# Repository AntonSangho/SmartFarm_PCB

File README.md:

# 프로젝트명 : 포르쉐 

# 요구사항 작성을 위한 질문 
- 수집하고자하는 환경데이터: 예) 온도, 습도  
- 휴대가능여부 
- 물리적인 사이즈 : 예) 휴대폰사이즈 , 카드지갑사이즈 
- 사용자가 손으로 제어하는 방식 : 예) 버튼
- 사용자가 동작을 확인하는 형태 : 예) LED, 부저음, 액정디스플레이
- 데이터를 확인하는 시각적인 결과물의 형태 : 예) 로우데이터, 그래프 
- 생각하는 키트의 외관 형태 
- 베터리로 동작하는 경우, 사용가능해야하는 대략적인 시간 
- 제작 수량

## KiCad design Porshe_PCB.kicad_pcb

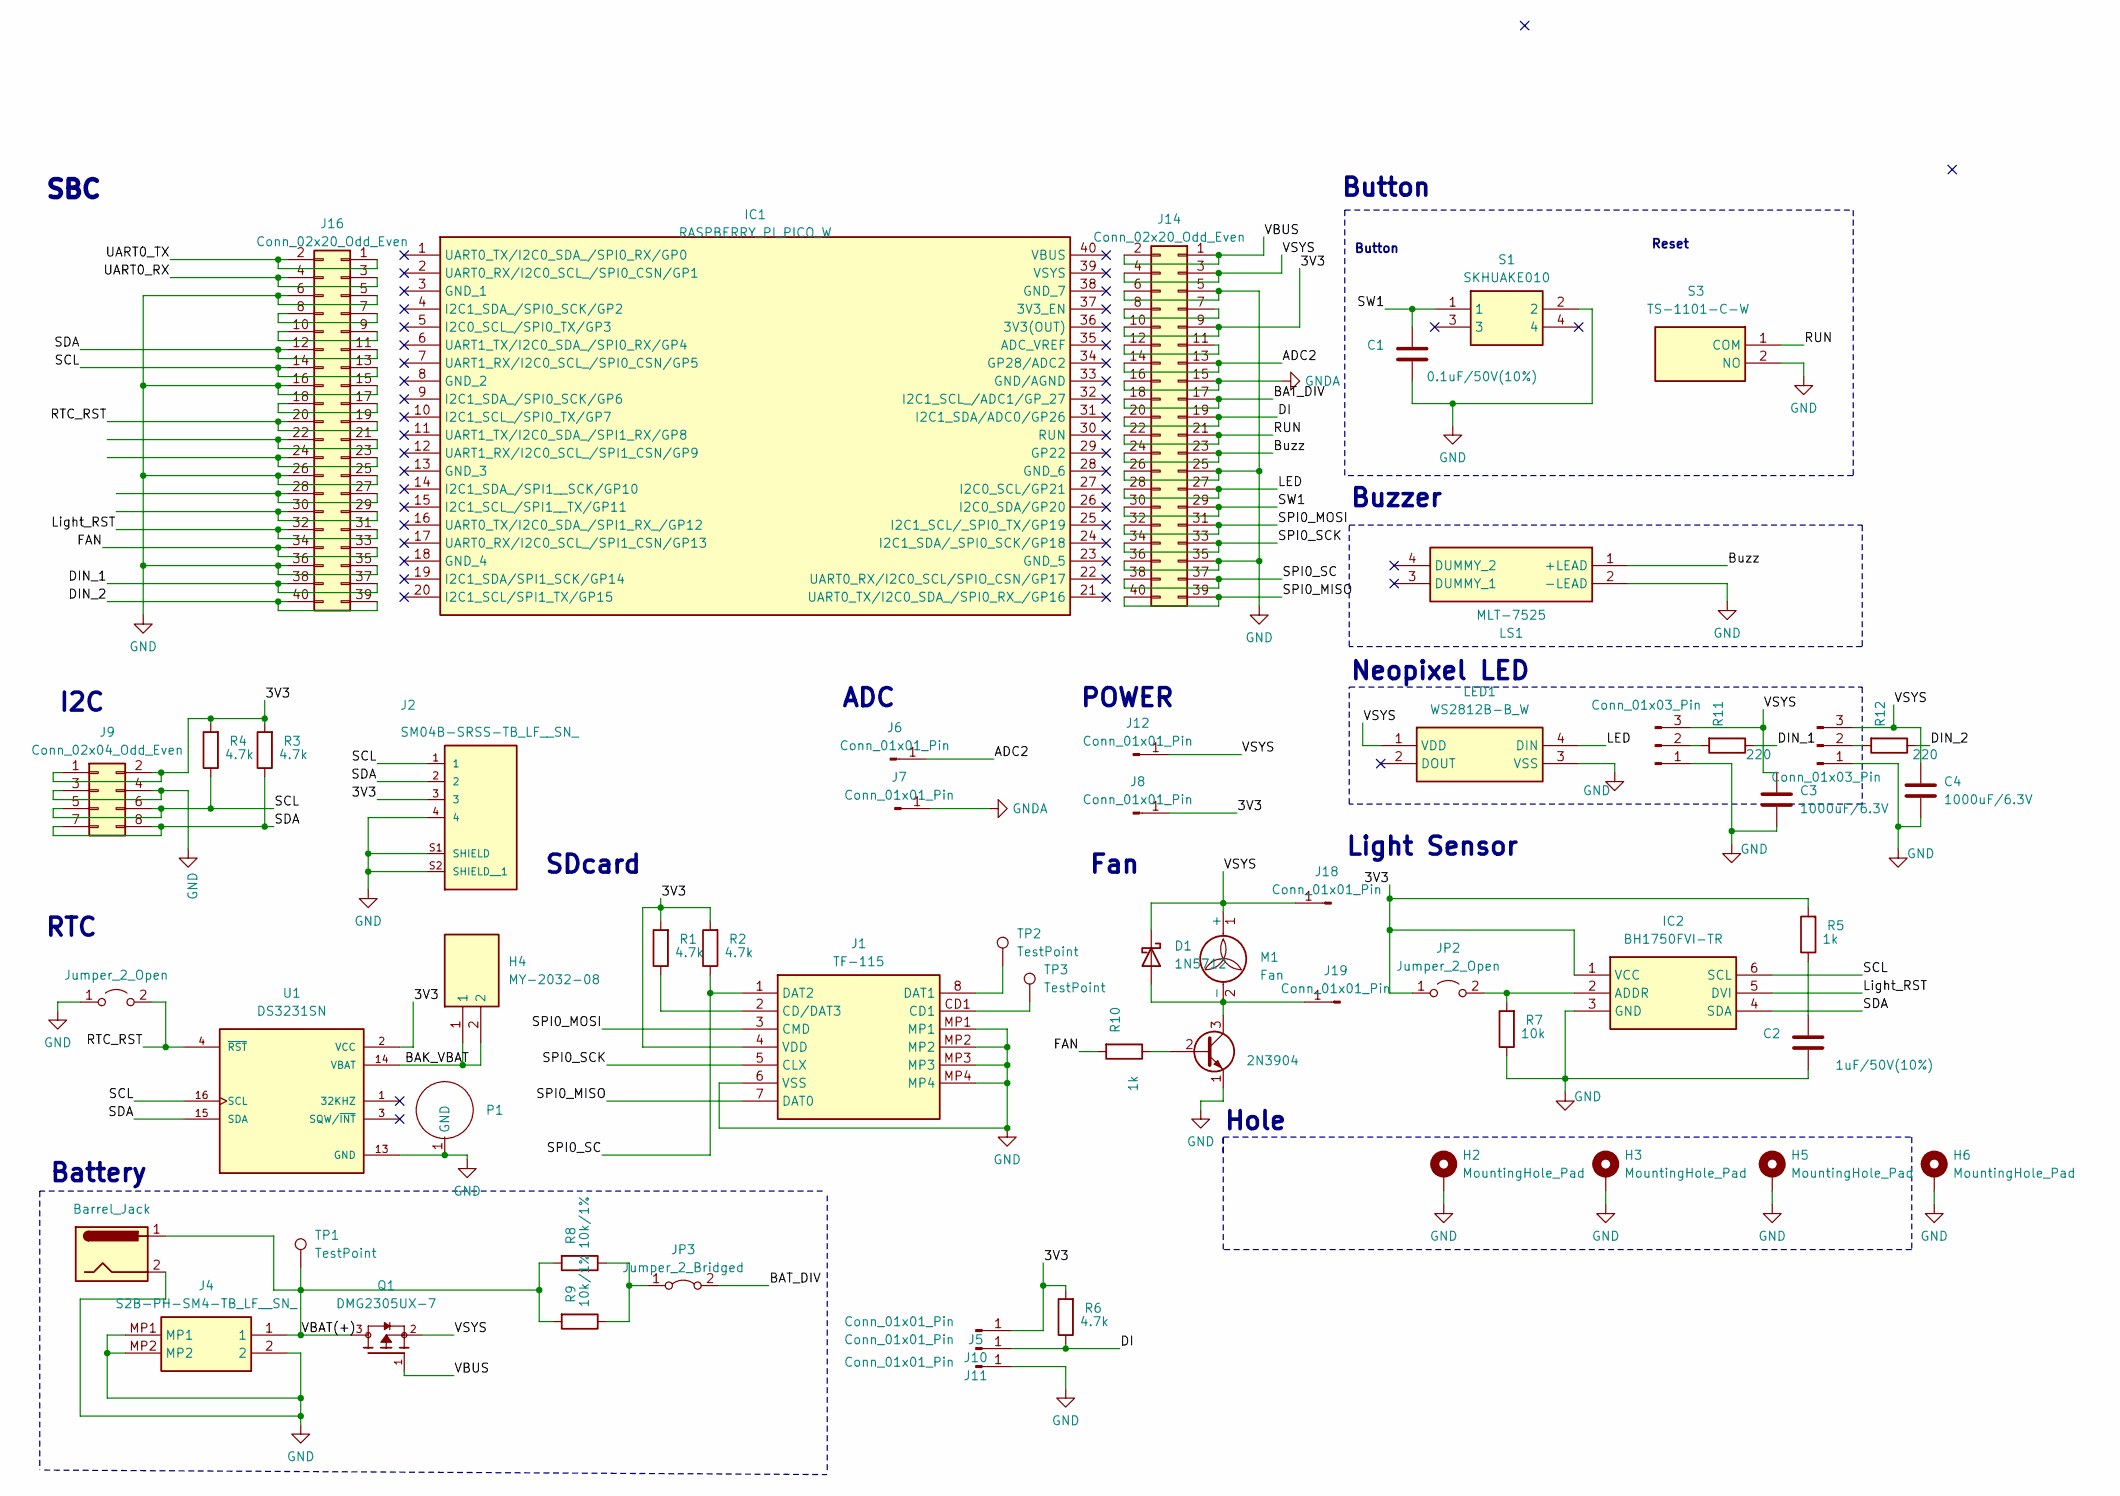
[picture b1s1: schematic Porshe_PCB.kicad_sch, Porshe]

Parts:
C1: 0.1uF/50V(10%); C_0603_1608Metric; LCSC Part # C14663
C2: 1uF/50V(10%); C_0603_1608Metric; LCSC Part # C14663
C3, C4: 1000uF/6.3V; CP_Radial_D8.0mm_P5.00mm
D1: 1N5712; D_DO-35_SOD27_P7.62mm_Horizontal
H2, H3, H5, H6: MountingHole_Pad; MountingHole_2.7mm_M2.5_ISO7380_Pad_TopOnly
H4: MY-2032-08; MY203208; Manufacturer_Part_Number MY-2032-08; JLCPCB Part # C964831
IC1: RASPBERRY_PI_PICO_W; RASPBERRYPIPICOW; Manufacturer_Part_Number RASPBERRY PI PICO W
IC2: BH1750FVI-TR; WSOF6; Manufacturer_Part_Number BH1750FVI-TR; Mouser Part Number 755-BH1750FVI-TR
J1: TF-115; TF115; Manufacturer_Part_Number TF-115; LCSC Part # C266620
J2: SM04B-SRSS-TB_LF__SN_; JST_SM04B-SRSS-TB_LF__SN_; LCSC Part # C160404
J4: S2B-PH-SM4-TB_LF__SN_; S2BPHSM4TBLFSN; Manufacturer_Part_Number S2B-PH-SM4-TB(LF)(SN); LCSC Part # C295747
J5, J10, J11, J12: Conn_01x01_Pin; TestPoint_THTPad_D2.0mm_Drill1.0mm
J6, J7, J8, J18, J19: Conn_01x01_Pin; Pin_D1.3mm_L11.0mm
J9: Conn_02x04_Odd_Even; PinSocket_2x04_P2.54mm_Vertical_SMD; LCSC Part # C5160819
J13: Barrel_Jack; BarrelJack_GCT_DCJ200-10-A_Horizontal
J14, J16: Conn_02x20_Odd_Even; PinSocket_2x20_P2.54mm_Vertical_SMD; LCSC Part # C3975165
J15, J17: Conn_01x03_Pin; PinHeader_1x03_P2.00mm_Vertical
JP1, JP2: Jumper_2_Open; SolderJumper-2_P1.3mm_Open_RoundedPad1.0x1.5mm
JP3: Jumper_2_Bridged; SolderJumper-2_P1.3mm_Bridged_RoundedPad1.0x1.5mm
LED1: WS2812B-B_W; WS2812BBW; Manufacturer_Part_Number WS2812B-B/W; JLCPCB Part # C2761795
LS1: MLT-7525; MLT7525; Manufacturer_Part_Number MLT-7525
M1: Fan
P1: CR2032_GND
Q1: DMG2305UX-7; SOT91P240X110-3N_DMG2305UX-7; PARTREV 09/2018; LCSC Part # C150470
Q2: 2N3904; TO-92_Inline
R1, R2, R3, R4, R6: 4.7k; R_0603_1608Metric_Pad0.98x0.95mm_HandSolder
R5, R10: 1k; R_0603_1608Metric_Pad0.98x0.95mm_HandSolder
R7: 10k; R_0603_1608Metric_Pad0.98x0.95mm_HandSolder
R8, R9: 10k/1%; R_0603_1608Metric_Pad0.98x0.95mm_HandSolder
R11, R12: 220; R_0603_1608Metric_Pad0.98x0.95mm_HandSolder
S1: SKHUAKE010; Manufacturer_Part_Number SKHUAKE010; Mouser Part Number 688-SKHUAKE010
S3: TS-1101-C-W; TS1101CW; Manufacturer_Part_Number TS-1101-C-W
TP1, TP2, TP3: TestPoint; TestPoint_Pad_D1.0mm
U1: DS3231SN; SOIC127P1032X265-16N

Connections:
/3V3: IC2.1 (VCC), J1.4 (VDD), J2.3, J5.1, J8.1, J9.1, J9.2, J14.9, J14.10, JP2.1 (A), R1.2, R2.2, R3.2, R4.2, R5.2, R6.2, U1.2 (VCC)
/ADC2: J6.1, J14.13, J14.14
/BAK_VBAT: H4.1, H4.2, U1.14 (VBAT)
/BAT_DIV: J14.17, J14.18, JP3.2 (B)
/Buzz: J14.23, J14.24, LS1.1 (+LEAD)
/DI: J10.1, J14.19, J14.20, R6.1
/DIN_1: J16.37, J16.38, R11.1
/DIN_2: J16.39, J16.40, R12.1
/FAN: J16.33, J16.34, R10.2
/LED: J14.27, J14.28, LED1.4 (DIN)
/Light_RST: IC2.5 (DVI), J16.31, J16.32
/RTC_RST: J16.19, J16.20, JP1.2 (B), U1.4 (~RST)
/RUN: J14.21, J14.22, S3.1 (COM)
/SCL: IC2.6 (SCL), J2.1, J9.5, J9.6, J16.13, J16.14, R4.1, U1.16 (SCL)
/SDA: IC2.4 (SDA), J2.2, J9.7, J9.8, J16.11, J16.12, R3.1, U1.15 (SDA)
/SPI0_MISO: J1.7 (DAT0), J14.39, J14.40
/SPI0_MOSI: J1.3 (CMD), J14.31, J14.32
/SPI0_SC: J1.1 (DAT2), J14.37, J14.38, R2.1
/SPI0_SCK: J1.5 (CLX), J14.33, J14.34
/SW1: C1.2, J14.29, J14.30, S1.1
/UART0_RX: J16.3, J16.4
/UART0_TX: J16.1, J16.2
/VBAT(+): J4.1, J13.1, Q1.3, R8.2, R9.2, TP1.1
/VBUS: J14.1, J14.2, Q1.1
/VSYS: C3.1, C4.1, D1.1 (K), J12.1, J14.3, J14.4, J15.3, J17.3, J18.1, LED1.1 (VDD), M1.1 (+), Q1.2
GND: C1.1, C2.1, C3.2, C4.2, H2.1, H3.1, H5.1, H6.1, IC2.3 (GND), J1.6 (VSS), J1.MP1, J1.MP2, J1.MP3, J1.MP4, J2.4, J2.S1 (SHIELD), J2.S2 (SHIELD__1), J4.2, J4.MP1, J4.MP2, J9.3, J9.4, J11.1, J13.2, J14.5, J14.6, J14.25, J14.26, J14.35, J14.36, J15.1, J16.5, J16.6, J16.15, J16.16, J16.25, J16.26, J16.35, J16.36, J17.1, JP1.1 (A), LED1.3 (VSS), LS1.2 (-LEAD), P1.1 (GND), Q2.1 (E), R7.1, S1.2, S3.2 (NO), U1.13 (GND)
GNDA: J7.1, J14.15, J14.16
unnamed: C2.2, R5.1
unnamed: D1.2 (A), J19.1, M1.2 (-), Q2.3 (C)
unnamed: IC2.2 (ADDR), JP2.2 (B), R7.2
unnamed: J1.2 (CD/DAT3), R1.1
unnamed: J1.8 (DAT1), TP2.1
unnamed: J1.CD1, TP3.1
unnamed: J14.7, J14.8
unnamed: J14.11, J14.12
unnamed: J15.2, R11.2
unnamed: J16.7, J16.8
unnamed: J16.9, J16.10
unnamed: J16.17, J16.18
unnamed: J16.21, J16.22
unnamed: J16.23, J16.24
unnamed: J16.27, J16.28
unnamed: J16.29, J16.30
unnamed: J17.2, R12.2
unnamed: JP3.1 (A), R8.1, R9.1
unnamed: Q2.2 (B), R10.1

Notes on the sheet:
Fan
Reset
I2C
POWER
Button
Button
Battery
RTC
Buzzer
Neopixel LED
SDcard
Hole
Light Sensor
ADC
SBC

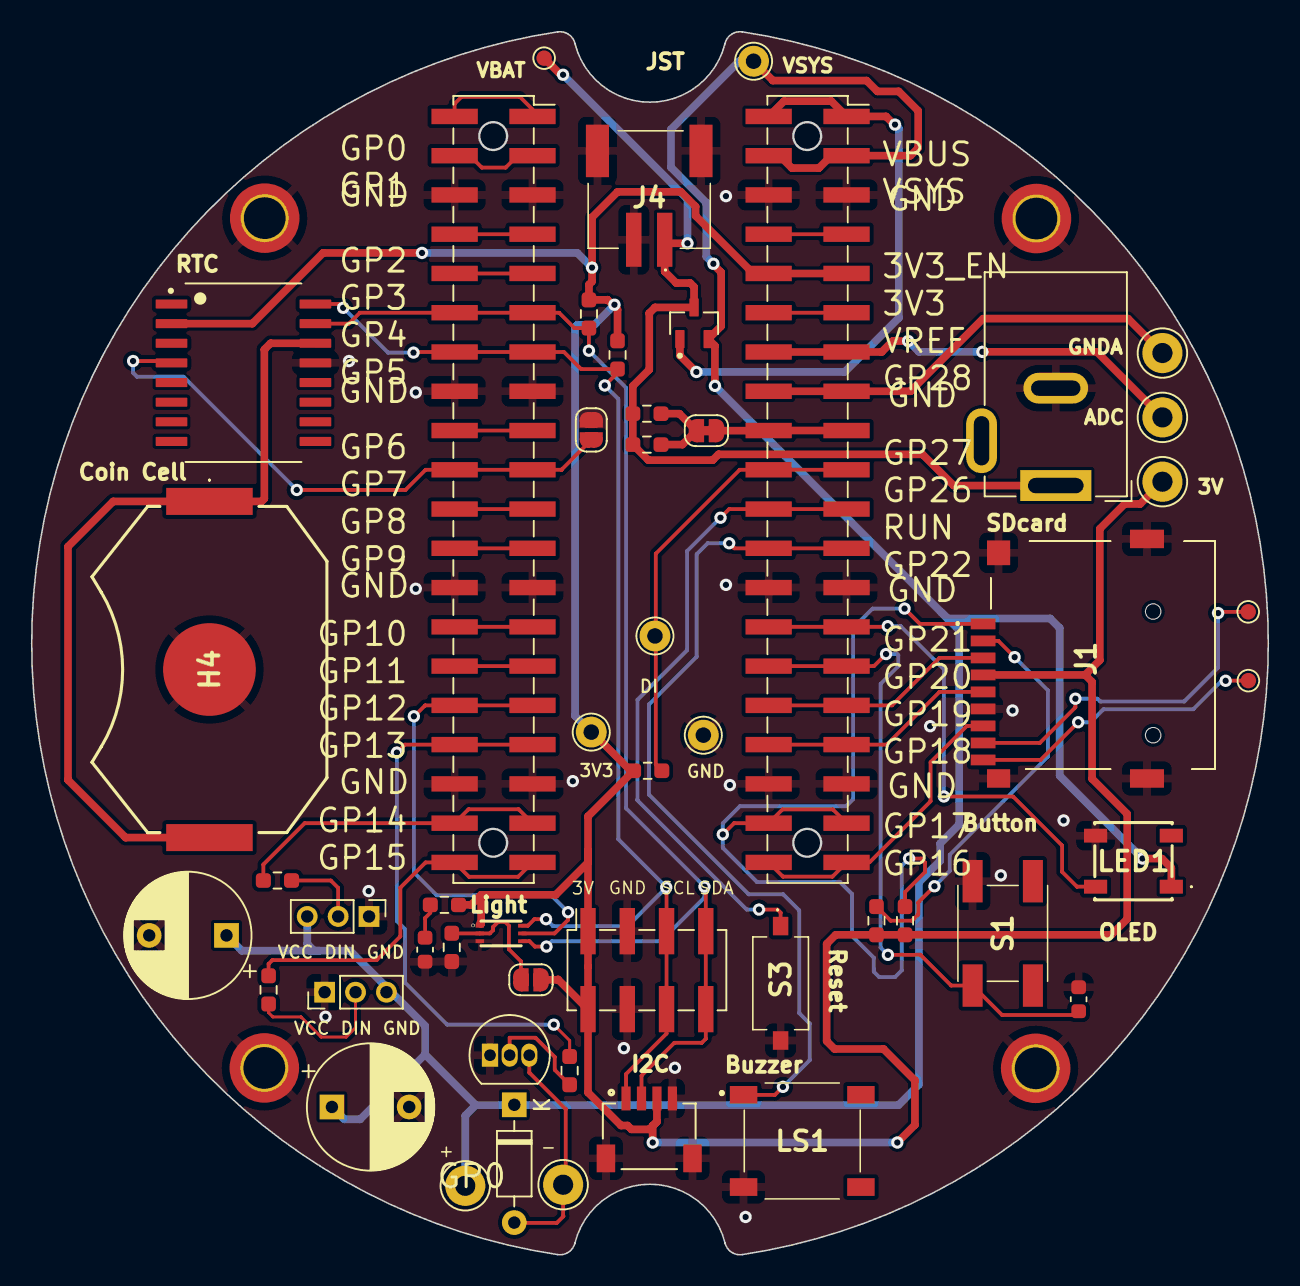
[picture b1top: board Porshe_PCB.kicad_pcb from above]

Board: 2 copper layers, 80.0 x 79.1 mm, 55 parts (0 on the bottom side), 46 nets.

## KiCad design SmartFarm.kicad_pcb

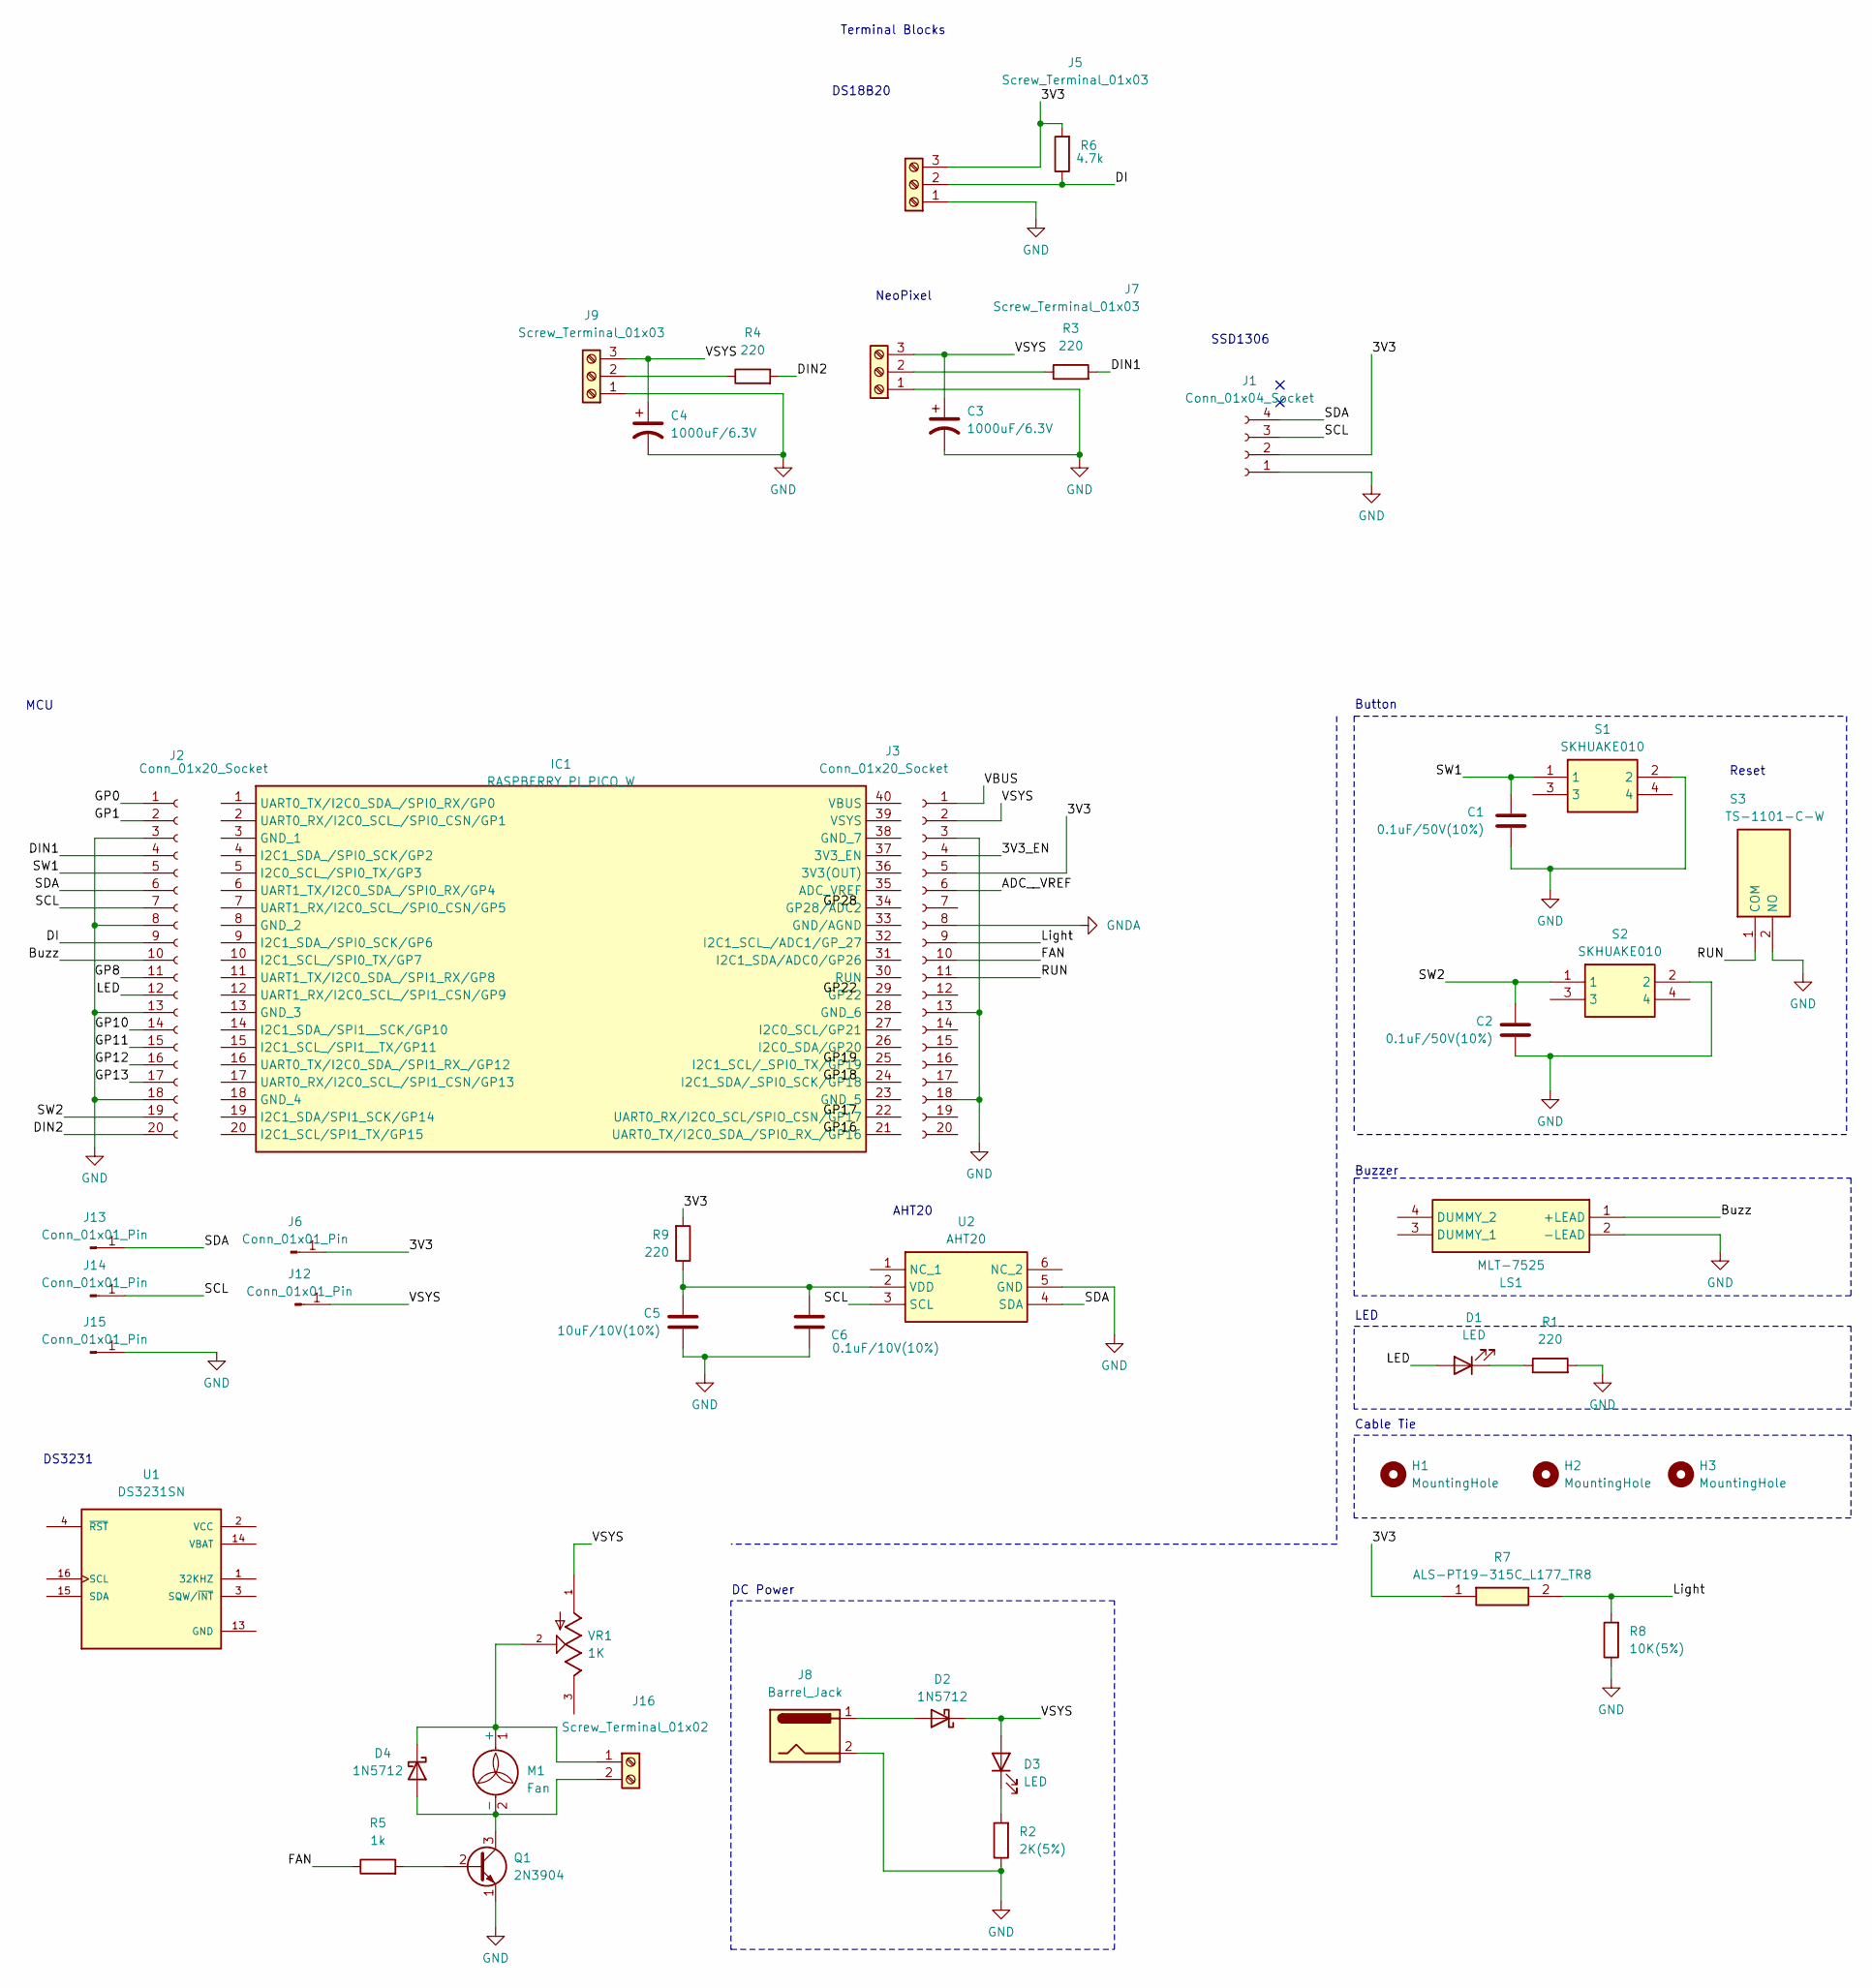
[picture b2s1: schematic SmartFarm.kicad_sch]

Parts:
C1, C2: 0.1uF/50V(10%); CP_EIA-1608-08_AVX-J_Pad1.25x1.05mm_HandSolder
C3, C4: 1000uF/6.3V; EEE0JA152UAP
C5: 10uF/10V(10%); CP_EIA-1608-10_AVX-L_Pad1.25x1.05mm_HandSolder
C6: 0.1uF/10V(10%); CP_EIA-1608-10_AVX-L_Pad1.25x1.05mm_HandSolder
D1, D3: LED; LED_0603_1608Metric_Pad1.05x0.95mm_HandSolder
D2, D4: 1N5712; SOD3716X115N
H1, H2, H3: MountingHole; MountingHole_3.2mm_M3
IC1: RASPBERRY_PI_PICO_W; RASPBERRYPIPICOW; Manufacturer_Part_Number RASPBERRY PI PICO W
J1: Conn_01x04_Socket; PinHeader_1x04_P2.54mm_Vertical_SMD_Pin1Left
J2: Conn_01x20_Socket; PinSocket_1x20_P2.54mm_Vertical_SMD_Pin1Left
J3: Conn_01x20_Socket; PinSocket_1x20_P2.54mm_Vertical_SMD_Pin1Right
J5, J7, J9: Screw_Terminal_01x03; TerminalBlock_4Ucon_1x03_P3.50mm_Horizontal
J6, J12, J13, J14, J15: Conn_01x01_Pin; TestPoint_THTPad_D2.0mm_Drill1.0mm
J8: Barrel_Jack; BarrelJack_GCT_DCJ200-10-A_Horizontal
J16: Screw_Terminal_01x02; TerminalBlock_4Ucon_1x02_P3.50mm_Horizontal
LS1: MLT-7525; MLT7525; Manufacturer_Part_Number MLT-7525
M1: Fan
Q1: 2N3904; 2N3904SRTKPS
R1, R9: 220; R_0603_1608Metric_Pad0.98x0.95mm_HandSolder
R2: 2K(5%); R_0603_1608Metric_Pad0.98x0.95mm_HandSolder
R3, R4: 220; R_Axial_DIN0204_L3.6mm_D1.6mm_P5.08mm_Horizontal
R5: 1k; R_0603_1608Metric_Pad0.98x0.95mm_HandSolder
R6: 4.7k; R_Axial_DIN0204_L3.6mm_D1.6mm_P5.08mm_Horizontal
R7: ALS-PT19-315C_L177_TR8; ALSPT19315CL177TR8; Manufacturer_Part_Number ALS-PT19-315C/L177/TR8; Mouser Part Number 638-ALSPT19315CL177
R8: 10K(5%); R_0603_1608Metric_Pad0.98x0.95mm_HandSolder
S1, S2: SKHUAKE010; Manufacturer_Part_Number SKHUAKE010; Mouser Part Number 688-SKHUAKE010
S3: TS-1101-C-W; TS1101CW; Manufacturer_Part_Number TS-1101-C-W
U1: DS3231SN; SOIC127P1032X265-16N
U2: AHT20; Manufacturer_Part_Number AHT20
VR1: 1K; TRIM_3362P-1-103; PARTREV 08/26/10

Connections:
/3V3: J1.2, J3.5, J5.3, J6.1, R6.2, R7.1 (COLLECTOR), R9.2
/3V3_EN: J3.4
/ADC__VREF: J3.6
/Buzz: J2.10, LS1.1 (+LEAD)
/DI: J2.9, J5.2, R6.1
/DIN1: J2.4, R3.2
/DIN2: J2.20, R4.2
/FAN: J3.10, R5.1
/GP0: J2.1
/GP1: J2.2
/GP8: J2.11
/GP10: J2.14
/GP11: J2.15
/GP12: J2.16
/GP13: J2.17
/LED: D1.2 (A), J2.12
/Light: J3.9, R7.2 (EMITTER), R8.2
/RUN: J3.11, S3.1 (COM)
/SCL: J1.3, J2.7, J14.1, U2.3 (SCL)
/SDA: J1.4, J2.6, J13.1, U2.4 (SDA)
/SW1: C1.2, J2.5, S1.1
/SW2: C2.2, J2.19, S2.1
/VBUS: J3.1
/VSYS: C3.1, C4.1, D2.1 (K), D3.2 (A), J3.2, J7.3, J9.3, J12.1, VR1.1
GND: C1.1, C2.1, C3.2, C4.2, C5.1, C6.1, J1.1, J2.3, J2.8, J2.13, J2.18, J3.3, J3.13, J3.18, J5.1, J7.1, J8.2, J9.1, J15.1, LS1.2 (-LEAD), Q1.1 (E), R1.2, R2.1, R8.1, S1.2, S2.2, S3.2 (NO), U2.5 (GND)
GNDA: J3.8
unnamed: D1.1 (K), R1.1
unnamed: D2.2 (A), J8.1
unnamed: D3.1 (K), R2.2
unnamed: D4.2 (A), J16.2, M1.2 (-), Q1.3 (C)
unnamed: D4.1 (K), J16.1, M1.1 (+), VR1.2
unnamed: J7.2, R3.1
unnamed: J9.2, R4.1
unnamed: Q1.2 (B), R5.2
unnamed: C5.2, C6.2, R9.1, U2.2 (VDD)

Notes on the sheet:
Reset
SSD1306
AHT20
Button
DS3231
Terminal Blocks
DC Power
Buzzer
LED
NeoPixel
Cable Tie
DS18B20
MCU

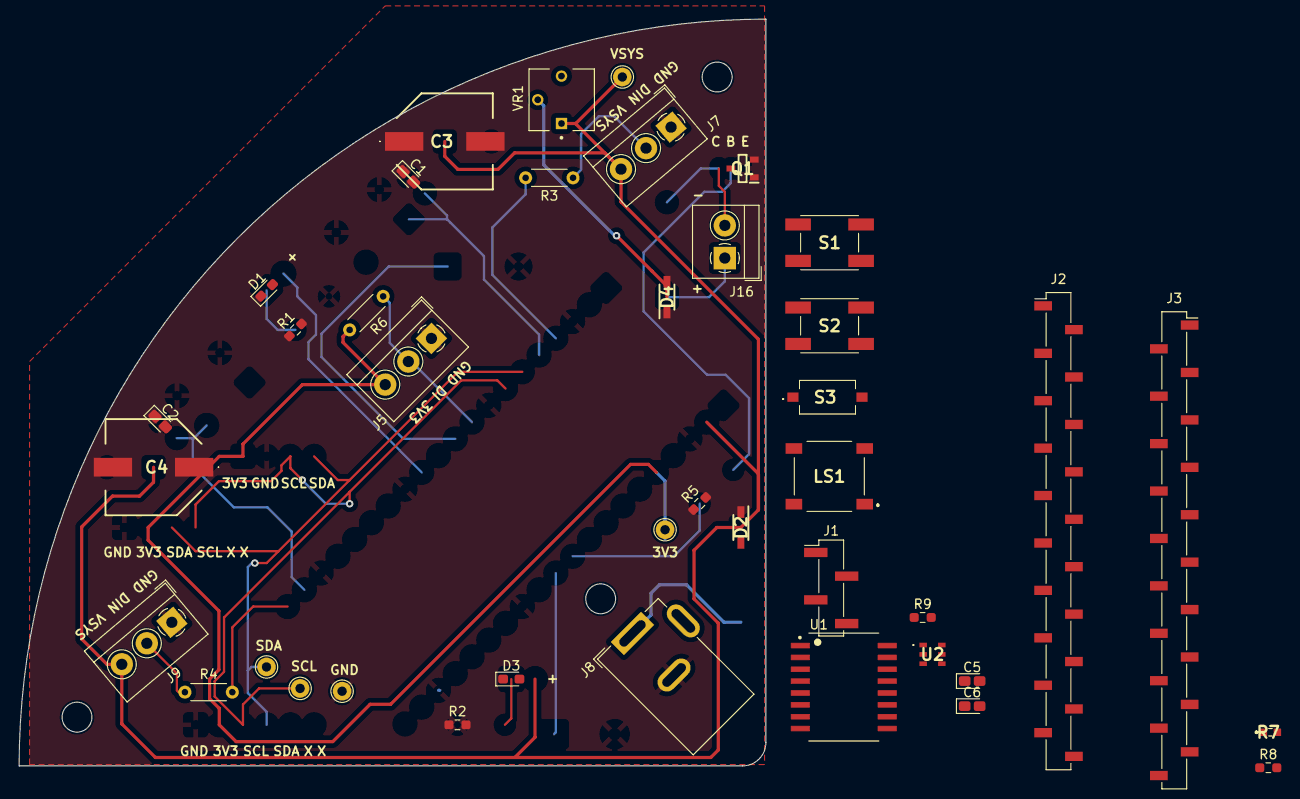
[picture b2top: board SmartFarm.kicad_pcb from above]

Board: 2 copper layers, 80.0 x 80.0 mm, 43 parts (0 on the bottom side), 24 nets.

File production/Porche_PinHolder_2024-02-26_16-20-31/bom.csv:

Designator,Footprint,Quantity,Value,LCSC Part #
C1,0603,1,0.1uF/50V(10%),C14663
C5,0603,1,10uF/10V(10%),C19702
C6,0603,1,0.1uF/10V(10%),C519438
H4,MY203208,1,MY-2032-08,C964831
"J14, J16",PinSocket_2x20_P2.54mm_Vertical_SMD,2,Conn_02x20_Odd_Even,C3975165
J2,JST_SM04B-SRSS-TB_LF__SN_,1,SM04B-SRSS-TB_LF__SN_,C160404
J3,PinSocket_2x02_P2.54mm_Vertical_SMD,1,Conn_02x02_Odd_Even,C3975147
J4,S2BPHSM4TBLFSN,1,S2B-PH-SM4-TB_LF__SN_,C295747
J5,TerminalBlock_4Ucon_1x03_P3.50mm_Horizontal,1,Screw_Terminal_01x03,C695630
J9,PinSocket_2x04_P2.54mm_Vertical_SMD,1,Conn_02x04_Odd_Even,C5160819
LED1,WS2812BBW,1,WS2812B-B_W,C2761795
LS1,MLT7525,1,MLT-7525,
Q1,SOT91P240X110-3N_DMG2305UX-7,1,DMG2305UX-7,C150470
"R3, R4, R6",0603,3,4.7k,
R7,ALSPT19315CL177TR8,1,ALS-PT19-315C_L177_TR8,C146233
R8,0603,1,10K(5%),
R9,0603,1,220,
S1,SKHUAKE010,1,SKHUAKE010,
S3,TS1101CW,1,TS-1101-C-W,
U1,SOIC127P1032X265-16N,1,DS3231SN,
U2,AHT20,1,AHT20,C2757850

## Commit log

2024-01-04 first init
2024-01-05 finish schematic
2024-01-05 layout left
2024-01-06 add potentialmeter and fan circuit
2024-01-06 layout done
2024-01-07 sample
2024-02-05 add pico w board
2024-02-20 add smd library parts
2024-02-24 schematic done
2024-02-24 코인베터리 접지추가
2024-02-24 오토라우팅완료
2024-02-26 BOM확인후 부품 배치완료
2024-03-05 sdcard라이브러리 추가
2024-03-05 회로도 완성
2024-03-06 add smartfarm function
2024-03-08 첫번째 완성
2024-03-08 오토라우딩하기전
2024-03-11 주문을 위한 버전
2024-03-29 add README.md
